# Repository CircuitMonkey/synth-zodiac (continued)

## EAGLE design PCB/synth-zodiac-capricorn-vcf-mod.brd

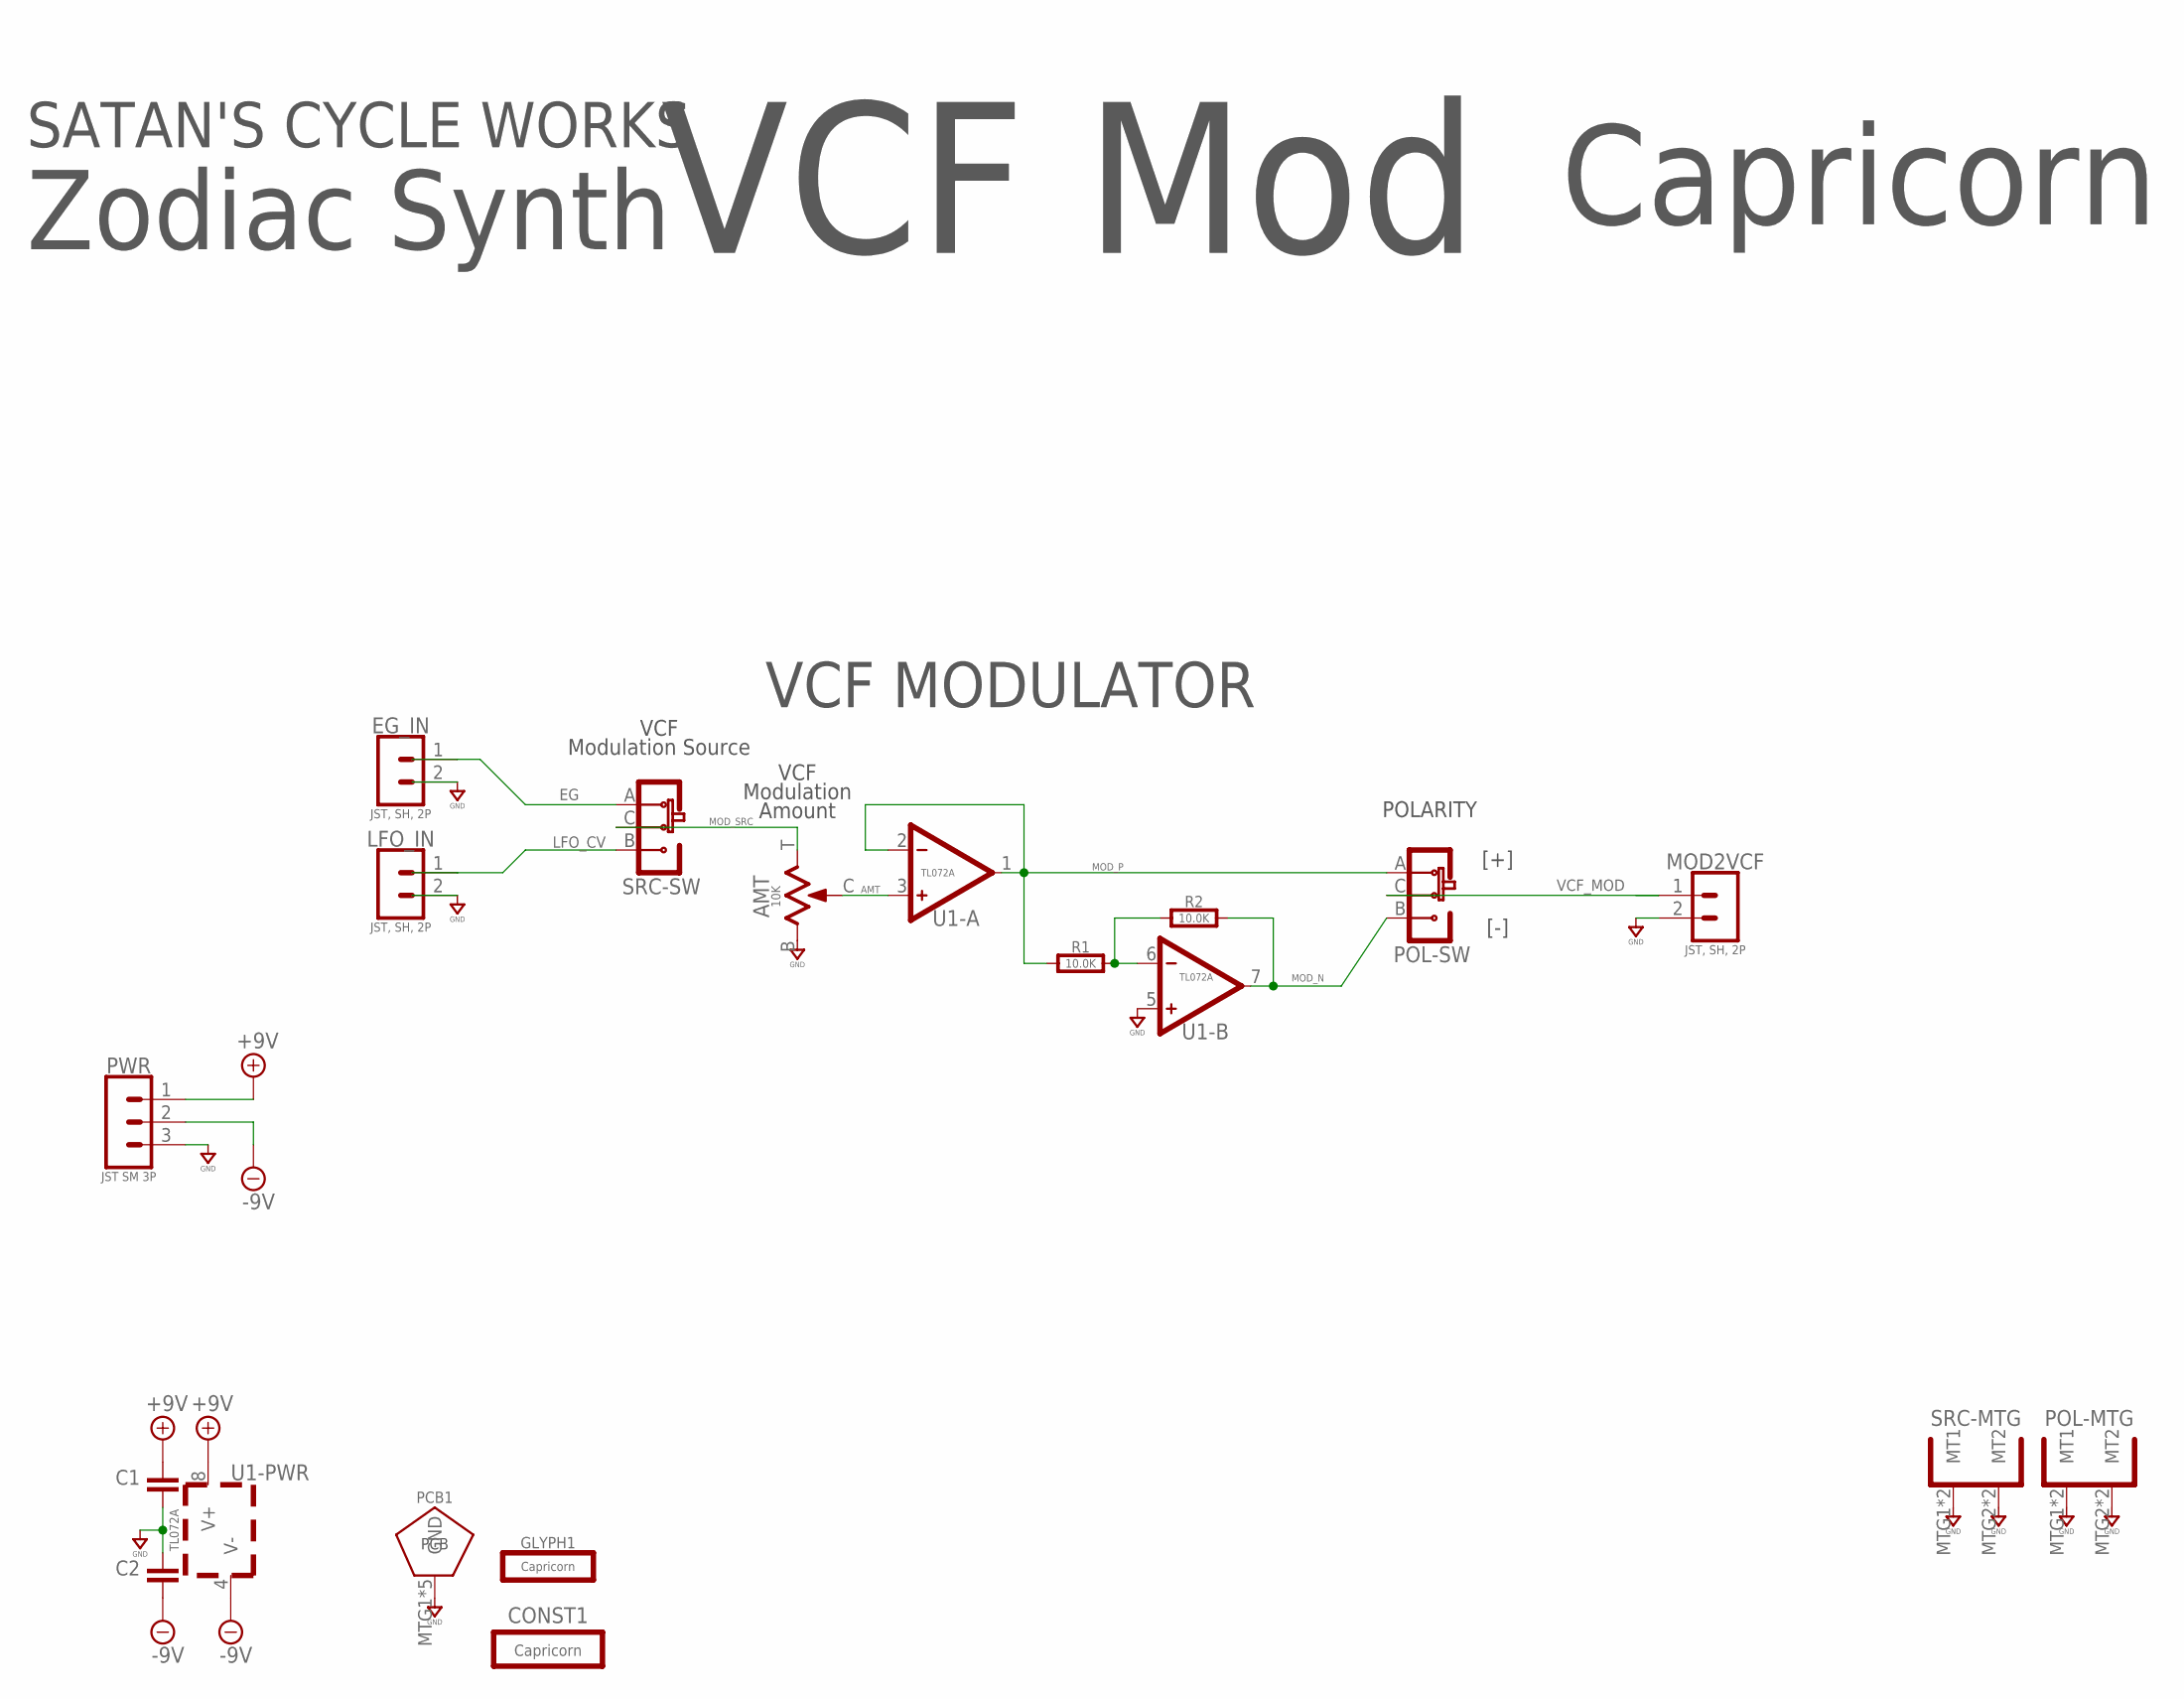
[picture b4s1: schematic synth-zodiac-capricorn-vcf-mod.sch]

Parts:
AMT: 10K; POT-RV9110
C1, C2: 0.1uF; 0603-CAP
CONST1: Capricorn; CAPRICORN-CONST
EG_IN: JST, SH, 2P; BM02B-SRSS-TB
GLYPH1: Capricorn; CAPRICORN-GLYPH
LFO_IN: JST, SH, 2P; BM02B-SRSS-TB
MOD2VCF: JST, SH, 2P; BM02B-SRSS-TB
PCB1: PCB FAB; PENTAGON-40MM-RAD
POL: SLIDE-SPDT-MNTSS-12-F45-TH-PCB-2; SS-12-F45-PNL-SMT-2
PWR: JST SM 3P; BM03B-SRSS-TB
R1, R2: 10.0K; 0603-RES
SRC: SLIDE-SPDT-MNTSS-12-F45-TH-PCB-2; SS-12-F45-PNL-SMT-2
U1: TL072A; SOP08

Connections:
+9V: C1.1, PWR.1, U1.8 (V+)
-9V: C2.2, PWR.2, U1.4 (V-)
AMT: AMT.C (2), U1.3 (+)
EG: EG_IN.1, SRC.A
GND: AMT.B (1), C1.2, C2.1, EG_IN.2, LFO_IN.2, MOD2VCF.2, PCB1.MTG1, PCB1.MTG2, PCB1.MTG3, PCB1.MTG4, PCB1.MTG5, POL.MTG1 (MT1), POL.MTG2 (MT2), POL.MTG3 (MT1), POL.MTG4 (MT2), PWR.3, SRC.MTG1 (MT1), SRC.MTG2 (MT2), SRC.MTG3 (MT1), SRC.MTG4 (MT2), U1.5 (+)
LFO_CV: LFO_IN.1, SRC.B
MOD_N: POL.B, R2.2, U1.7 (OUT)
MOD_P: POL.A, R1.1, U1.1 (OUT), U1.2 (-)
MOD_SRC: AMT.T (3), SRC.C
unnamed: R1.2, R2.1, U1.6 (-)
VCF_MOD: MOD2VCF.1, POL.C

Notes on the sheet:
POLARITY
VCF MODULATOR
VCF Modulation Source
[+]
[-]
VCF Modulation Amount
VCF Mod
Zodiac Synth
Capricorn
SATAN'S CYCLE WORKS

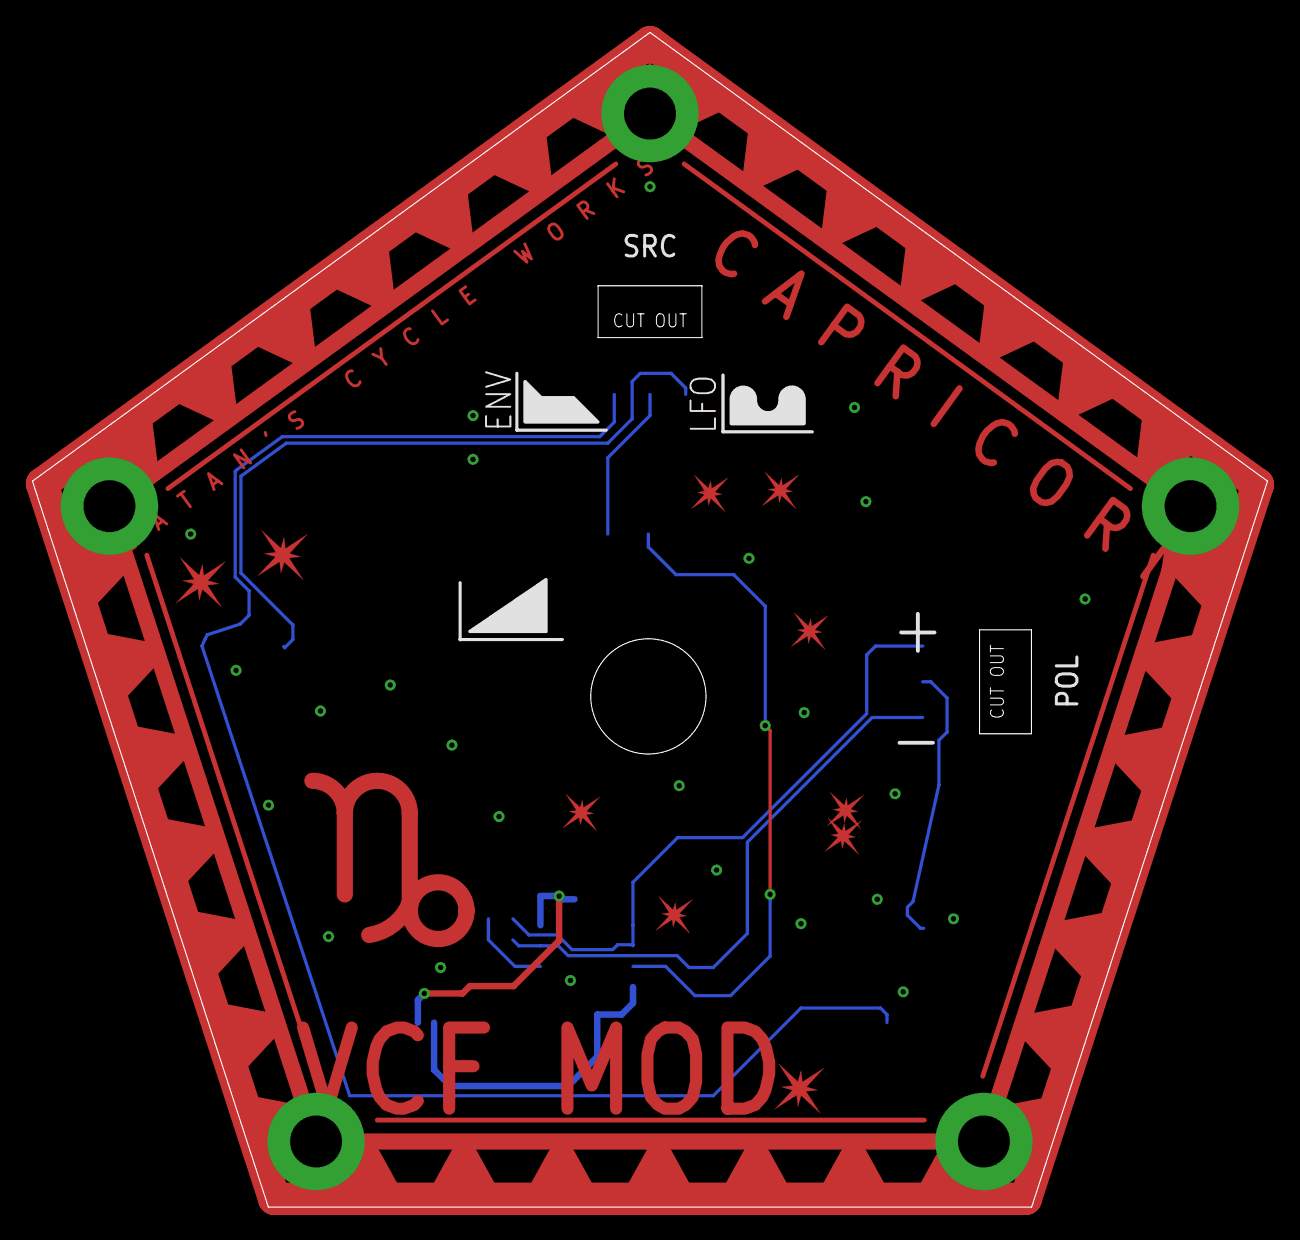
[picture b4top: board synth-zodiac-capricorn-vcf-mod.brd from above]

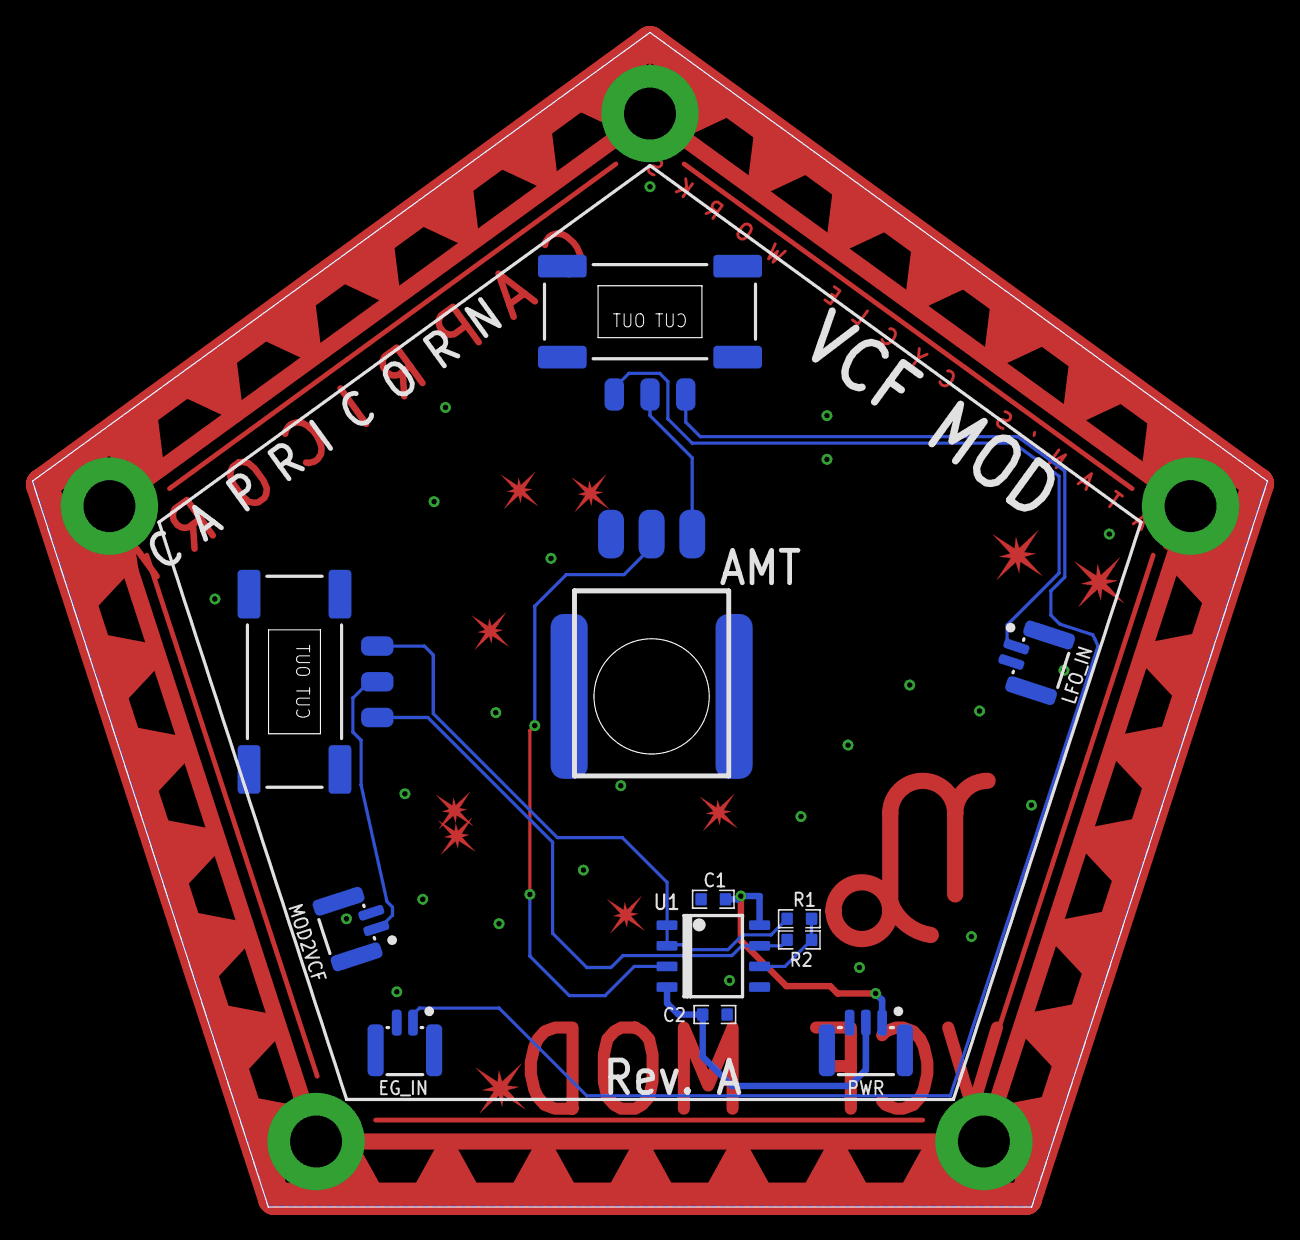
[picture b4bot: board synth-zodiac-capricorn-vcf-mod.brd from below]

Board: 2 copper layers, 76.1 x 72.4 mm, 15 parts (10 on the bottom side), 11 nets.

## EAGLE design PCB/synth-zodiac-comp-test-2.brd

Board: 2 copper layers, 4 parts (0 on the bottom side), 2 nets, no tracks yet.

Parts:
J1: USB-C, POWER; GCT-USB4515-PANEL
J2: USB-C, PWR; UJC-HP-3-SMT-TR-PANEL
SW1: Switch, DPDT; CK_OS202013MT5-PNL-SMT-2
SW2: SS-12-F45-PNL-SMT-2

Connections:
GND: J1.GNDA, J1.GNDB, J2.BNGB, J2.GNDA
VBUS: J1.VA, J1.VB, J2.VB-A, J2.VB-B

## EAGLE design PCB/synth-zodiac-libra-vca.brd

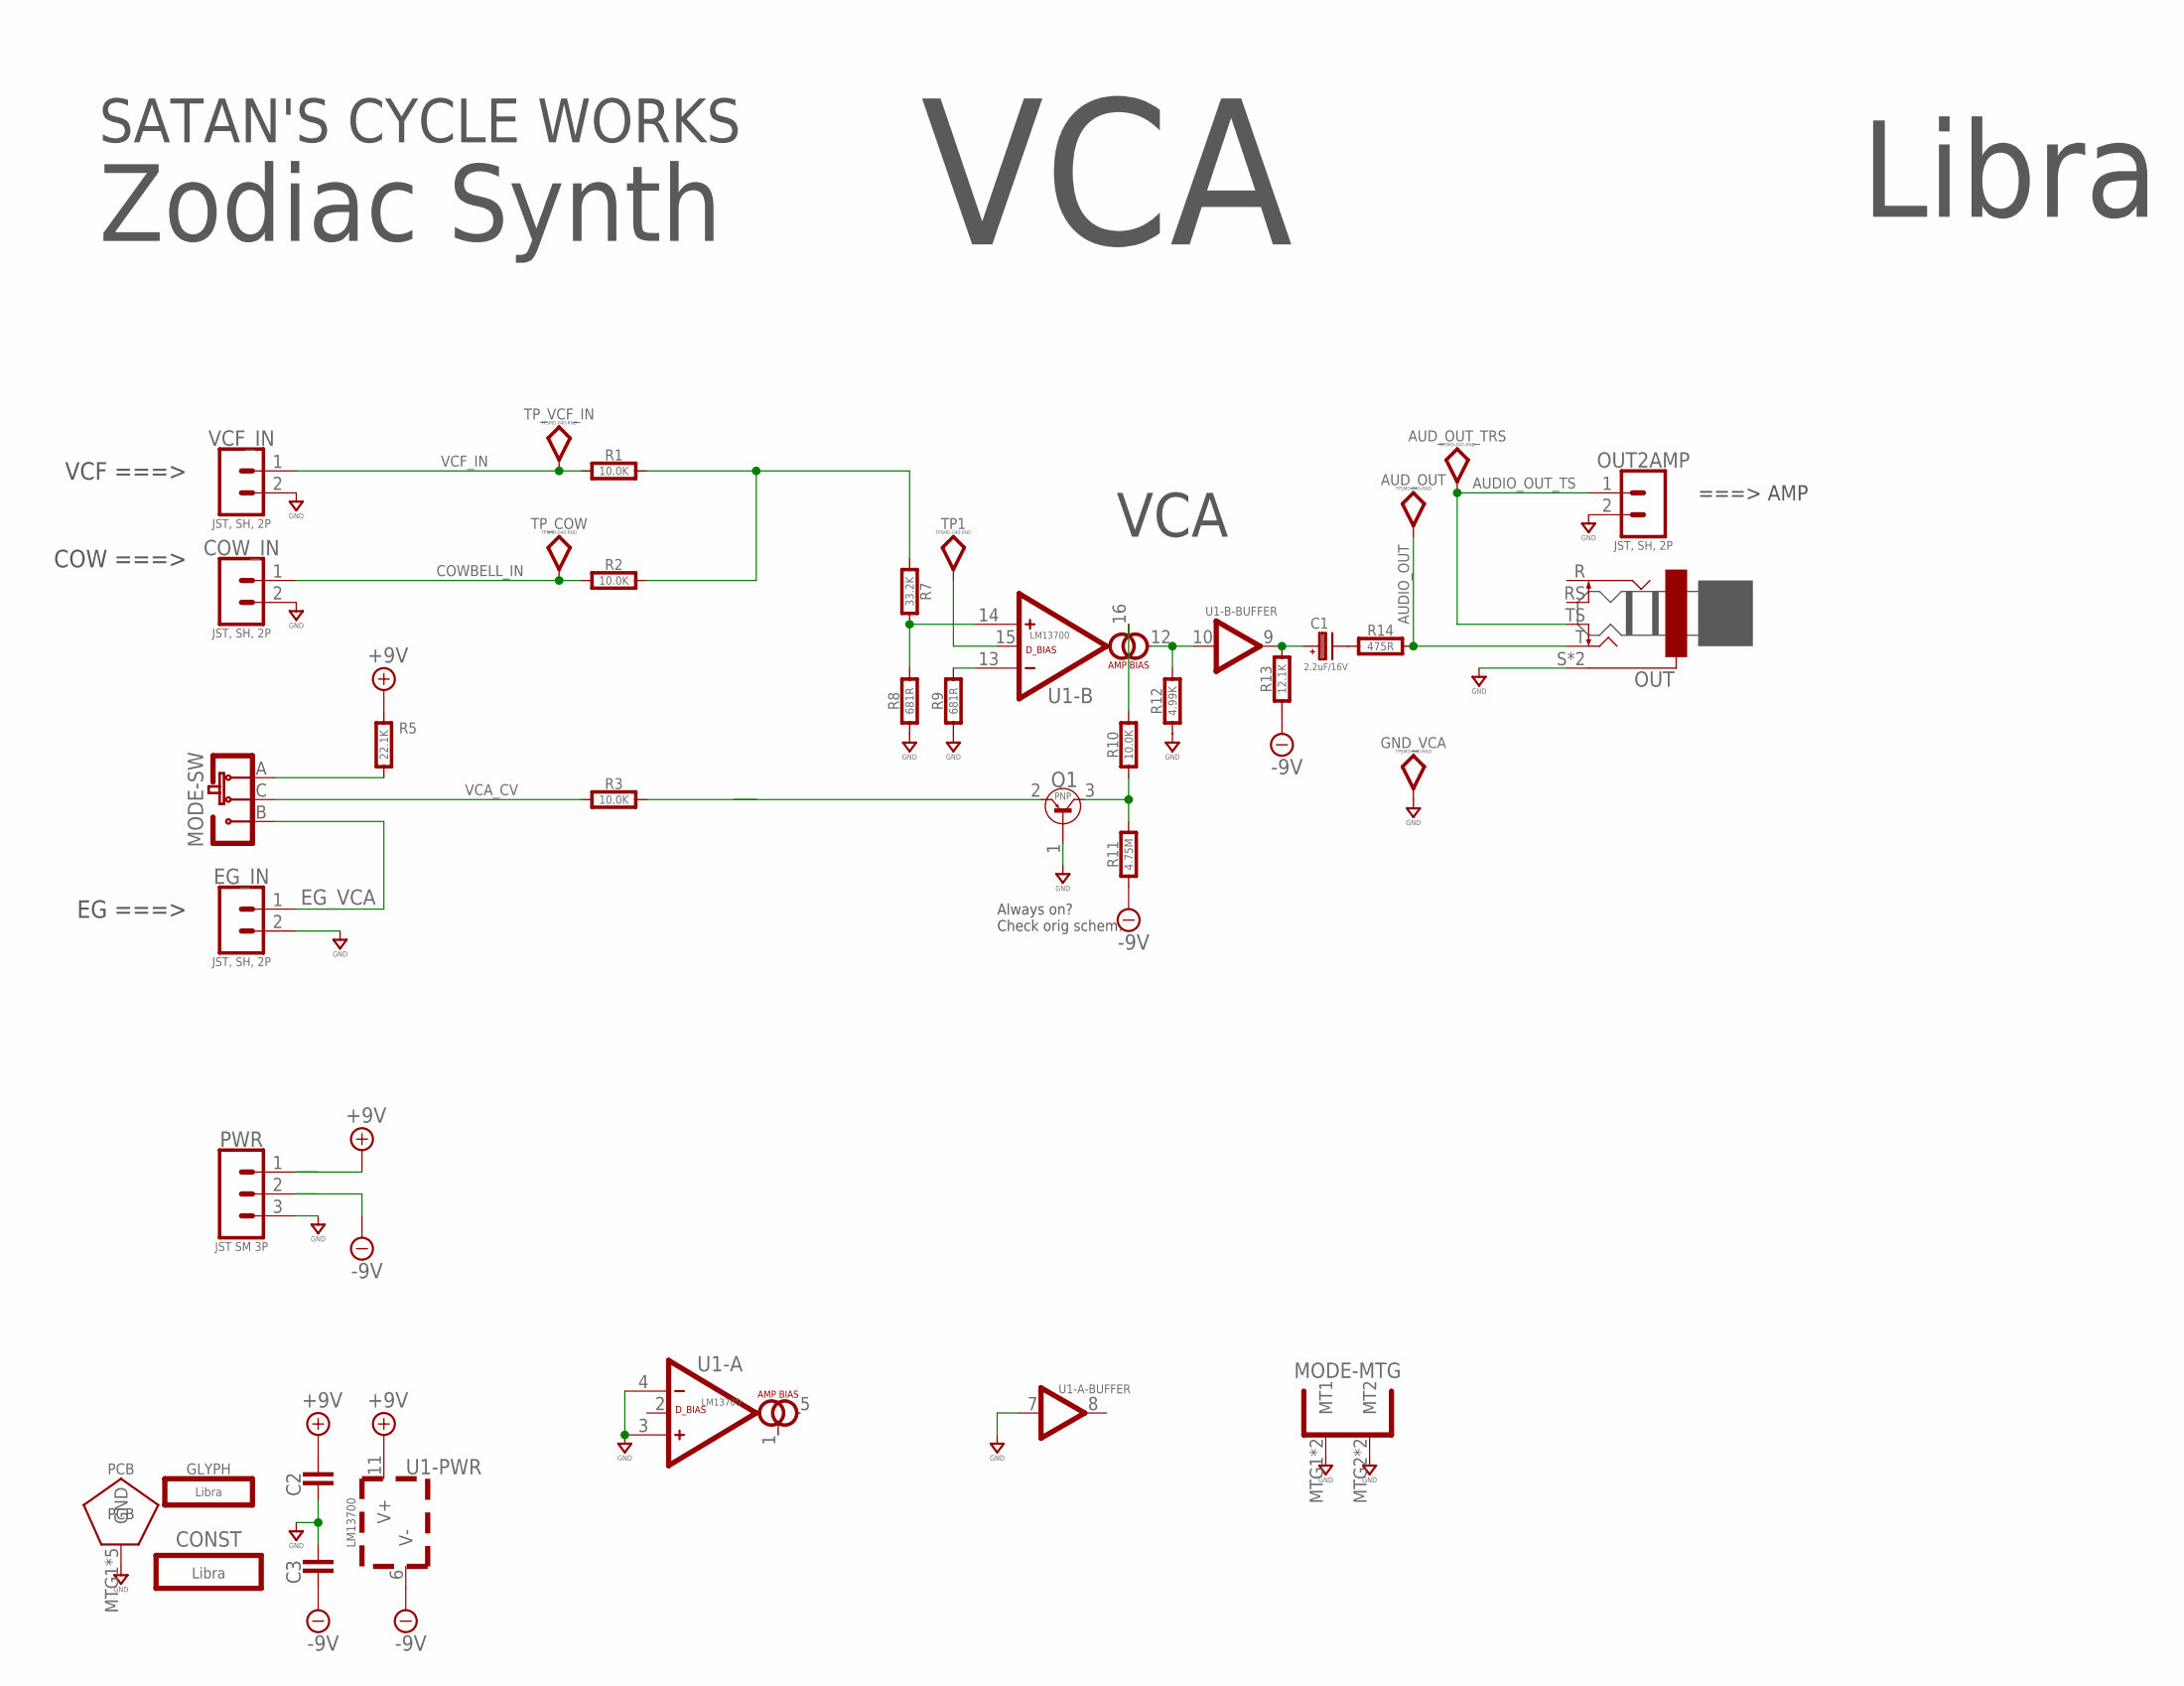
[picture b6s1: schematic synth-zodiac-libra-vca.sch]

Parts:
AUD_OUT: TPSMD-040-RND; SMD-040MIL-RND
AUD_OUT_TRS: TPSMD-040-RND; SMD-040MIL-RND
C1: 2.2uF/16V; CAP_ALUM_SMT_4
C2, C3: 0.1uF; 0603-CAP
CONST: Libra; LIBRA-CONST
COW_IN: JST, SH, 2P; BM02B-SRSS-TB
EG_IN: JST, SH, 2P; BM02B-SRSS-TB
GLYPH: Libra; LIBRA-GLYPH
GND_VCA: TPSMD-040-RND; SMD-040MIL-RND
MODE: SLIDE-SPDT-MNTSS-12-F45-TH-PCB-2; SS-12-F45-PNL-SMT-2
OUT: 6.35MM JACK; PNL-6.35-SMT-PADS
OUT2AMP: JST, SH, 2P; BM02B-SRSS-TB
PCB: PCB FAB; PENTAGON-40MM-RAD
PWR: JST SM 3P; BM03B-SRSS-TB
Q1: PNP; SOT-23
R1, R2, R3, R10: 10.0K; 0603-RES
R5: 22.1K; 0603-RES
R7: 33.2K; 0603-RES
R8, R9: 681R; 0603-RES
R11: 4.75M; 0603-RES
R12: 4.99K; 0603-RES
R13: 12.1K; 0603-RES
R14: 475R; 0603-RES
TP1: TPSMD-040-RND; SMD-040MIL-RND
TP_COW: TPSMD-040-RND; SMD-040MIL-RND
TP_VCF_IN: TPSMD-040-RND; SMD-040MIL-RND
U1: LM13700; SO16
VCF_IN: JST, SH, 2P; BM02B-SRSS-TB

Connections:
+9V: C2.2, PWR.1, R5.2, U1.11 (V+)
-9V: C3.1, PWR.2, R11.1, R13.1, U1.6 (V-)
AUDIO_OUT: AUD_OUT.TP, OUT.T, R14.2
AUDIO_OUT_TS: AUD_OUT_TRS.TP, OUT.TS (TN), OUT2AMP.1
COWBELL_IN: COW_IN.1, R2.1, TP_COW.TP
EG_VCA: EG_IN.1, MODE.B
GND: C2.1, C3.2, COW_IN.2, EG_IN.2, GND_VCA.TP, MODE.MTG1 (MT1), MODE.MTG2 (MT2), MODE.MTG3 (MT1), MODE.MTG4 (MT2), OUT.S, OUT.SS (S), OUT2AMP.2, PCB.MTG1, PCB.MTG2, PCB.MTG3, PCB.MTG4, PCB.MTG5, PWR.3, Q1.1 (BASE), R8.1, R9.1, R12.1, U1.3 (+), U1.4 (-), U1.7 (IN), VCF_IN.2
unnamed: R9.2, U1.13 (-)
unnamed: R7.2, R8.2, U1.14 (+)
unnamed: TP1.TP, U1.15 (DIODE-BIAS)
unnamed: R12.2, U1.10 (IN), U1.12 (OUT)
unnamed: R10.2, U1.16 (AMP-BIAS)
unnamed: C1.POS, R13.2, U1.9 (OUT)
unnamed: C1.NEG (N), R14.1
unnamed: Q1.3 (COLLECTOR), R10.1, R11.2
unnamed: Q1.2 (EMITTER), R3.2
unnamed: MODE.A, R5.1
VCA_CV: MODE.C, R3.1
VCF_IN: R1.1, TP_VCF_IN.TP, VCF_IN.1
VCF_OUT: R1.2, R2.2, R7.1

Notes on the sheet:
VCA
Always on? Check orig schem.
===> AMP
VCF ===>
EG ===>
COW ===>
Zodiac Synth
Libra
SATAN'S CYCLE WORKS

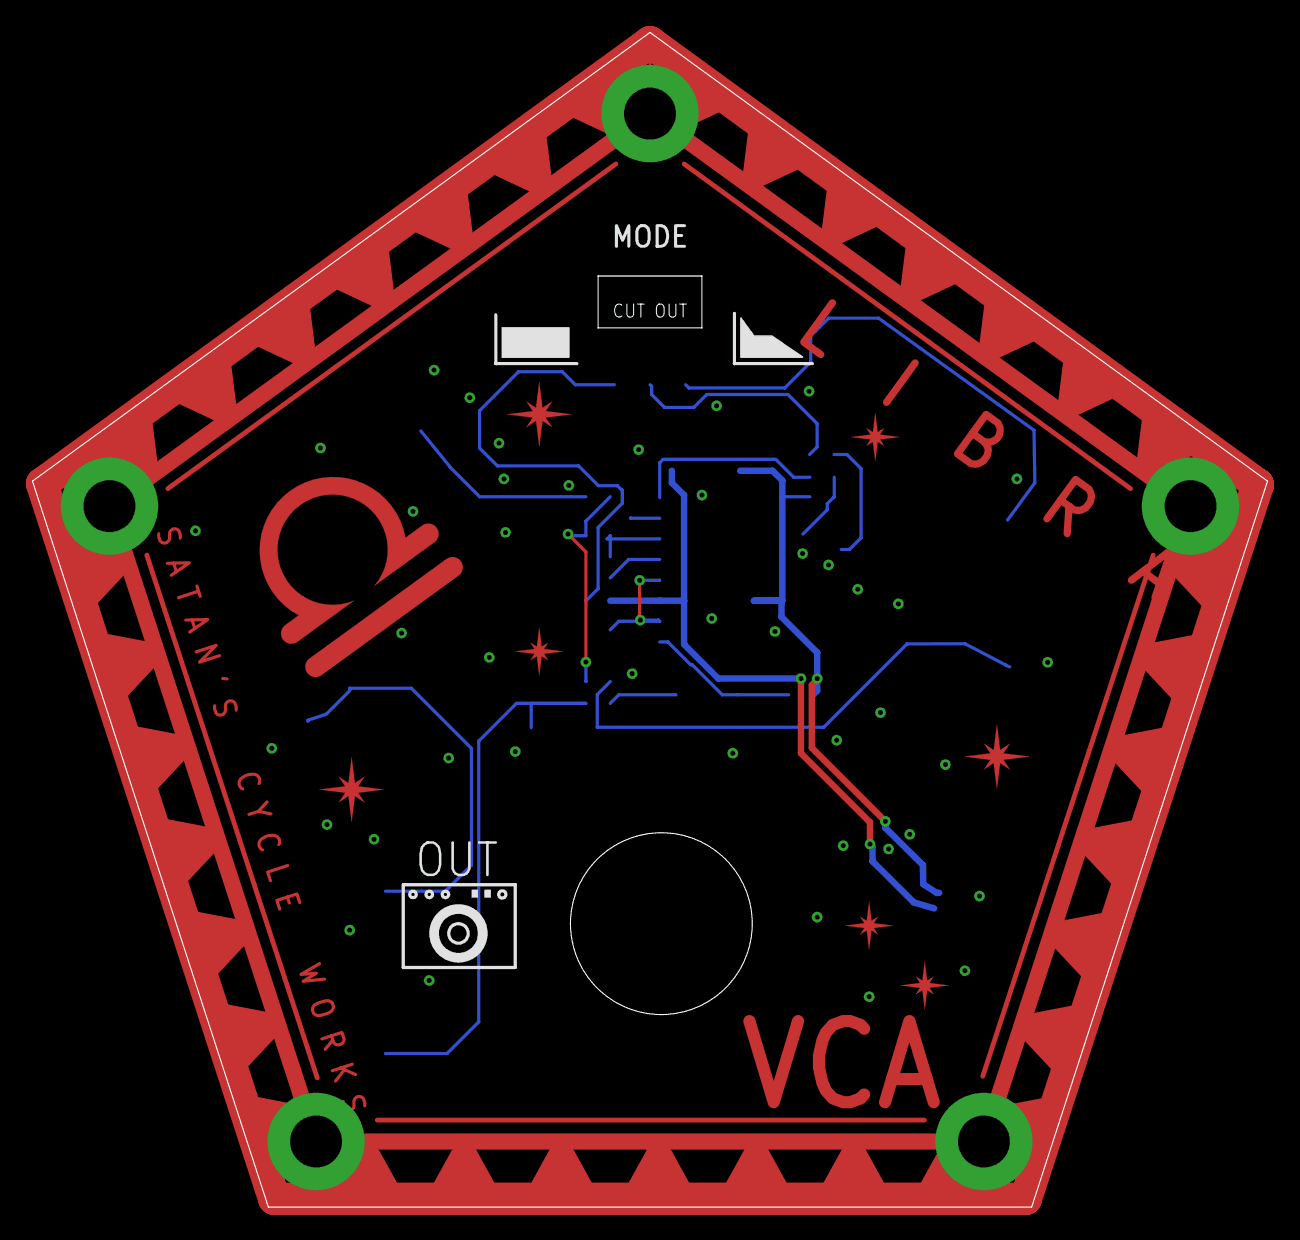
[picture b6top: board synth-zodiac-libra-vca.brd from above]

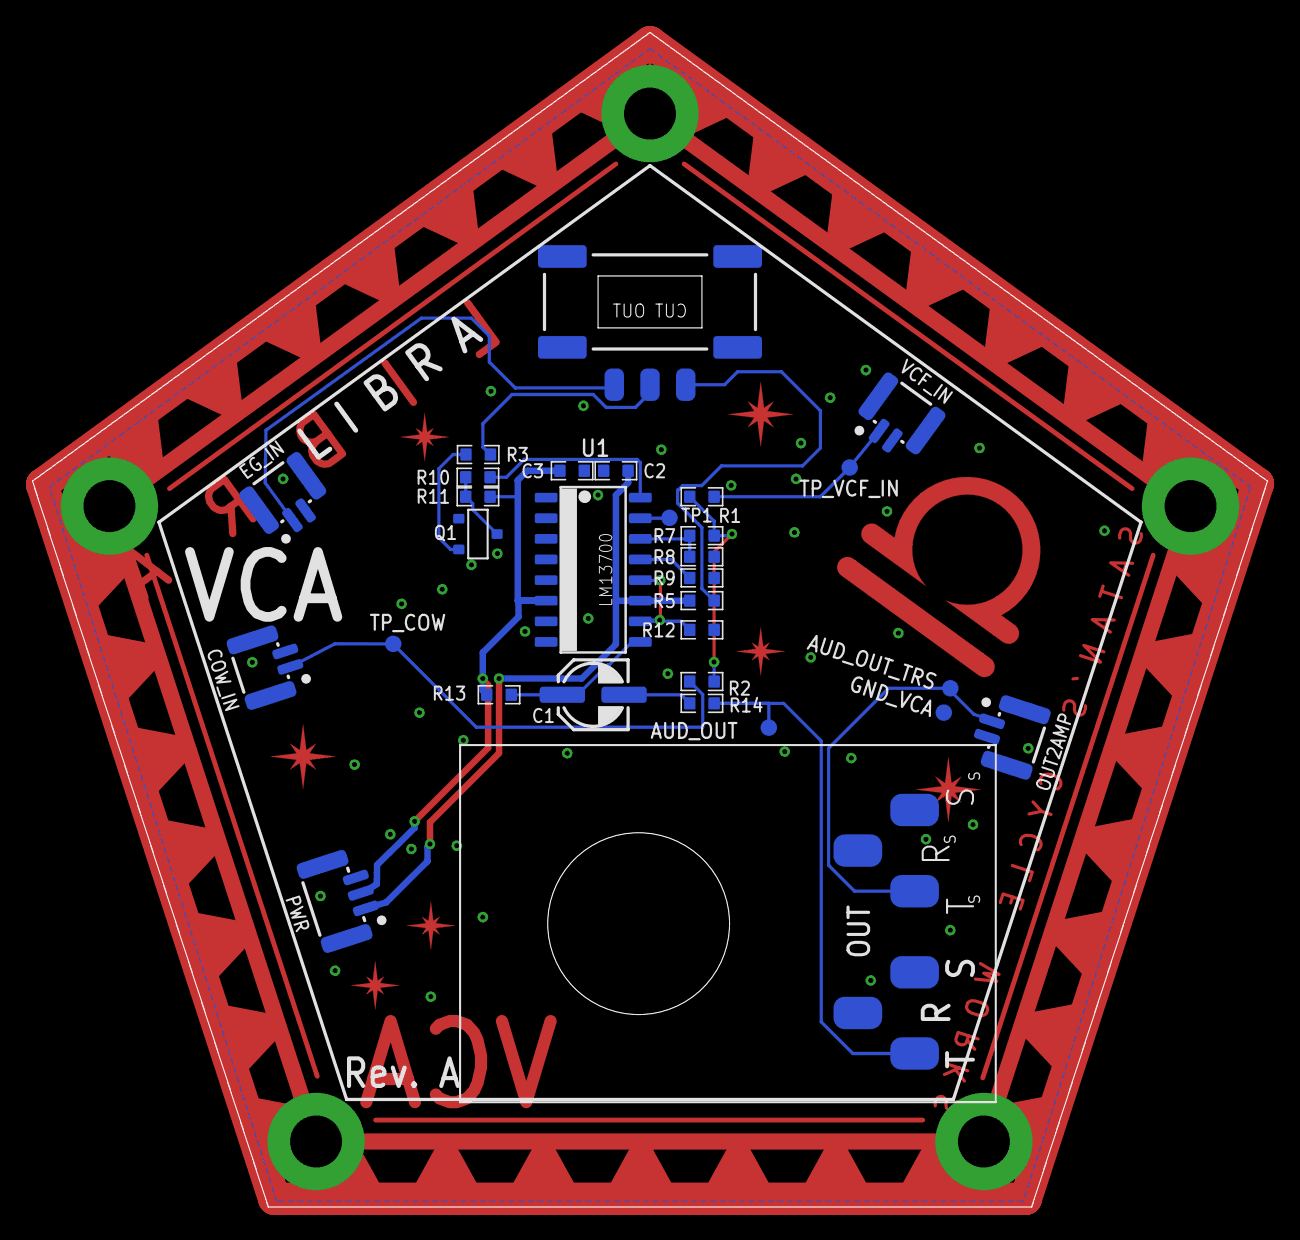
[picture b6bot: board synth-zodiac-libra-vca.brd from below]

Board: 2 copper layers, 76.1 x 72.4 mm, 33 parts (29 on the bottom side), 20 nets.
